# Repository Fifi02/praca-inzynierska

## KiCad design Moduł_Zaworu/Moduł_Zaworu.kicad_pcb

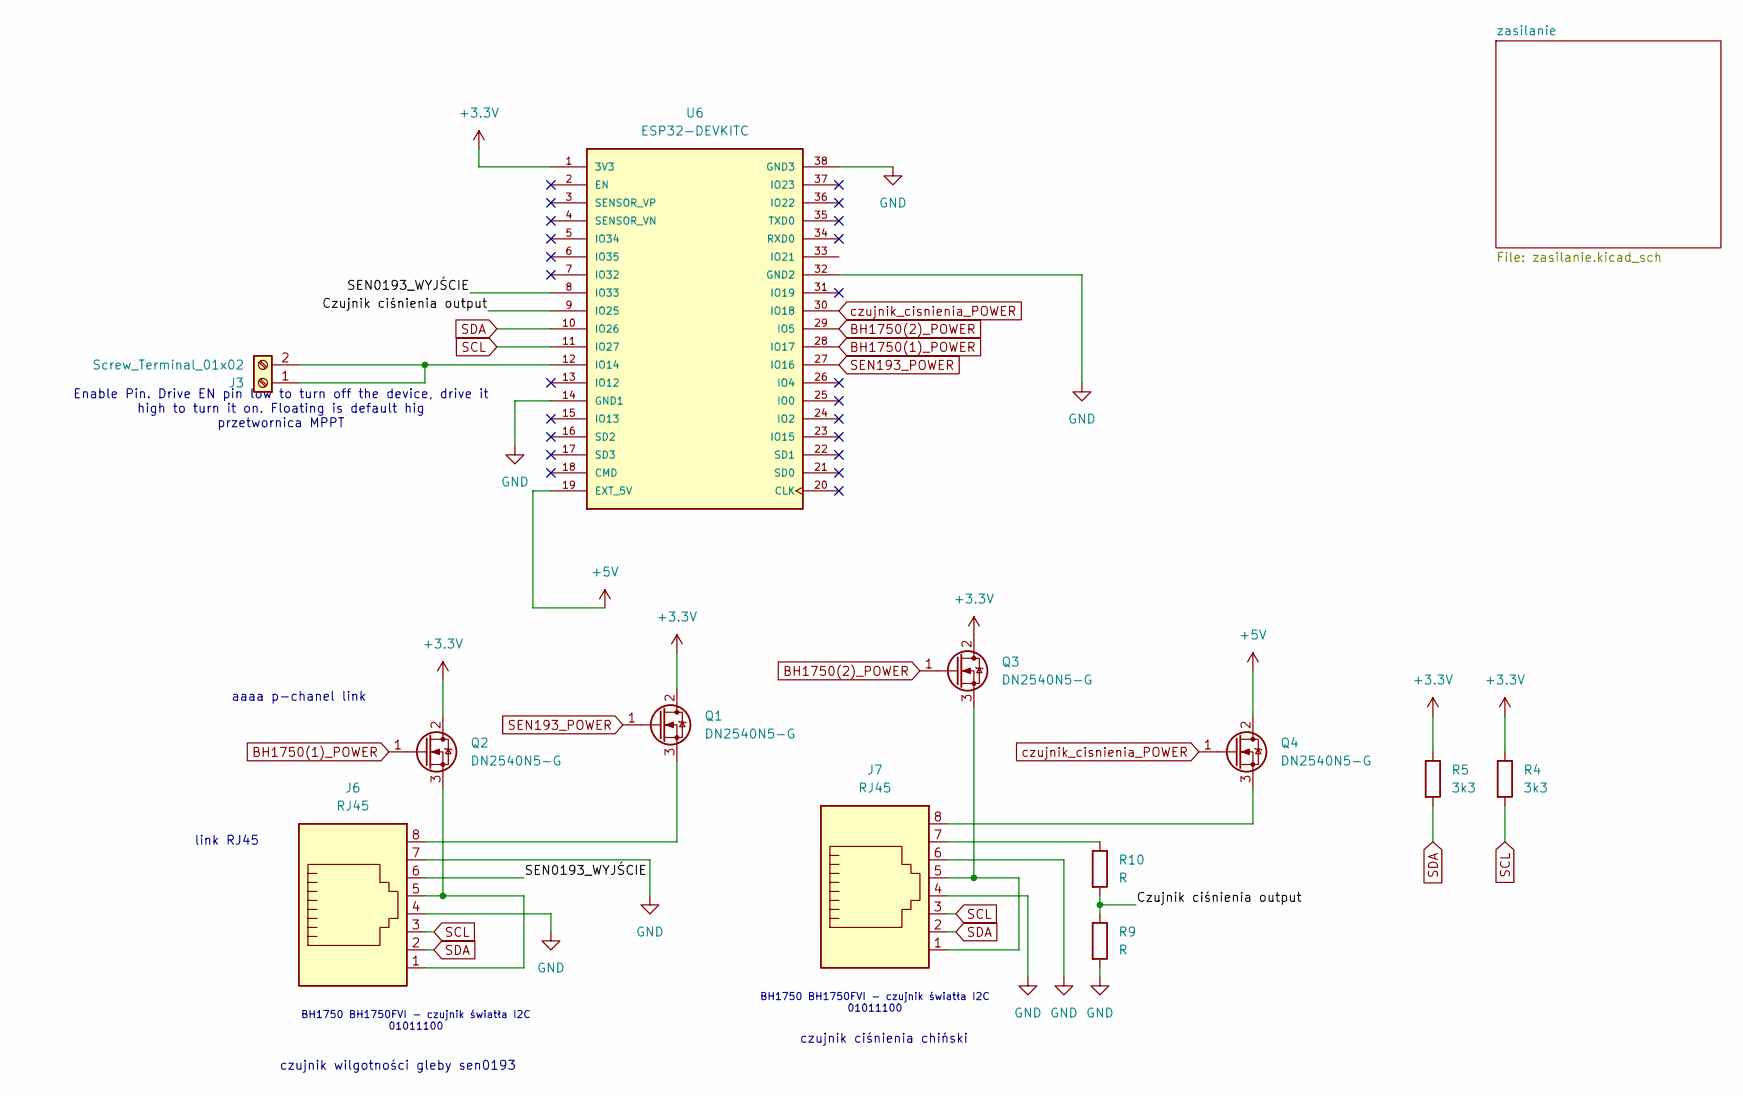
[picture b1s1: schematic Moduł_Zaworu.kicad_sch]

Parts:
J3: Screw_Terminal_01x02; TerminalBlock_Xinya_XY308-2.54-2P_1x02_P2.54mm_Horizontal
J6, J7: RJ45; RJ45_Amphenol_54602-x08_Horizontal
Q1, Q2, Q3, Q4: DN2540N5-G; SOT-23_Handsoldering
R4, R5: 3k3; R_1206_3216Metric
R9, R10: R; R_1206_3216Metric
U6: ESP32-DEVKITC; MODULE_ESP32-DEVKITC; PARTREV N/A

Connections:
+3.3V: Q1.2 (D), Q2.2 (D), Q3.2 (D), R4.1, R5.1, U6.1 (3V3); also elsewhere on the board
+5V: Q4.2 (D), U6.19 (EXT_5V); also elsewhere on the board
/Czujnik ciśnienia output: R9.1, R10.2, U6.9 (IO25)
/SEN0193_WYJŚCIE: J6.6, U6.8 (IO33)
BH1750(1)_POWER: Q2.1 (G), U6.28 (IO17)
BH1750(2)_POWER: Q3.1 (G), U6.29 (IO5)
GND: J6.4, J6.7, J7.4, J7.6, R9.2, U6.14 (GND1), U6.32 (GND2), U6.38 (GND3); also elsewhere on the board
unnamed: J3.1, J3.2, U6.12 (IO14)
unnamed: J7.7, R10.1
unnamed: J6.8, Q1.3 (S)
unnamed: J6.1, J6.5, Q2.3 (S)
unnamed: J7.1, J7.5, Q3.3 (S)
unnamed: J7.8, Q4.3 (S)
SCL: J6.3, J7.3, R4.2, U6.11 (IO27); also elsewhere on the board
SDA: J6.2, J7.2, R5.2, U6.10 (IO26); also elsewhere on the board
SEN193_POWER: Q1.1 (G), U6.27 (IO16)
czujnik_cisnienia_POWER: Q4.1 (G), U6.30 (IO18)

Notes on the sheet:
BH1750 BH1750FVI - czujnik światła I2C 01011100
Enable Pin. Drive EN pin low to turn off the device, drive it high to turn it on. Floating is default hig przetwornica MPPT
link RJ45
aaaa p-chanel link
czujnik wilgotności gleby sen0193
czujnik ciśnienia chiński

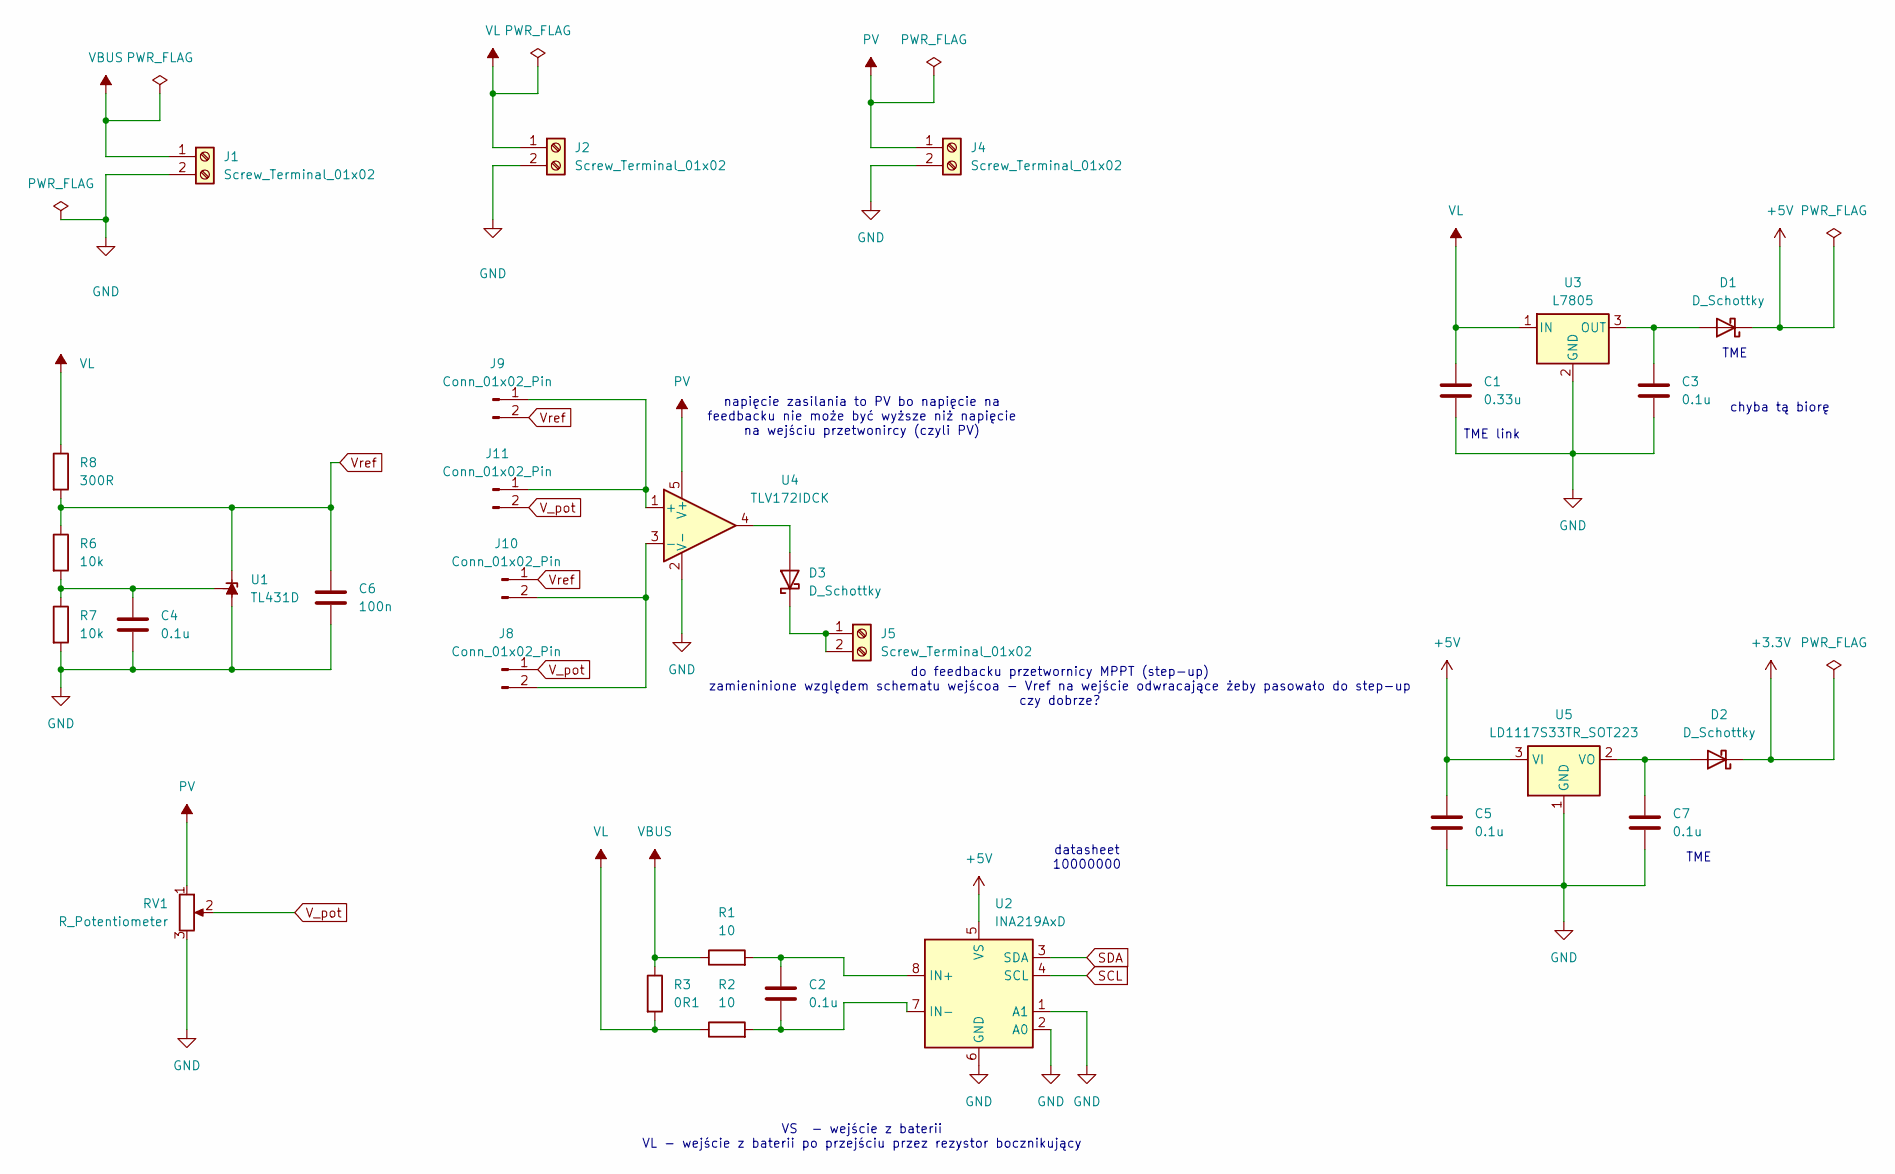
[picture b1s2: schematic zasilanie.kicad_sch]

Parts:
C1: 0.33u; CP_Elec_4x5.4
C2, C3, C4, C5, C7: 0.1u; C_Disc_D3.0mm_W1.6mm_P2.50mm
C6: 100n; C_Disc_D3.0mm_W1.6mm_P2.50mm
D1, D2, D3: D_Schottky; D_1206_3216Metric
J1, J2, J4: Screw_Terminal_01x02; TerminalBlock_MaiXu_MX126-5.0-02P_1x02_P5.00mm
J5: Screw_Terminal_01x02; TerminalBlock_Xinya_XY308-2.54-2P_1x02_P2.54mm_Horizontal
J8, J9, J10, J11: Conn_01x02_Pin; PinHeader_1x02_P2.54mm_Vertical
R1, R2: 10; R_1206_3216Metric
R3: 0R1; R_1206_3216Metric
R6, R7: 10k; R_1206_3216Metric
R8: 300R; R_1206_3216Metric
RV1: R_Potentiometer; Potentiometer_Bourns_3386W_Horizontal
U1: TL431D; SOIC-8_3.9x4.9mm_P1.27mm
U2: INA219AxD; SOIC-8_3.9x4.9mm_P1.27mm
U3: L7805; TO-220-3_Vertical
U4: TLV172IDCK; SOIC-8_5.3x5.3mm_P1.27mm
U5: LD1117S33TR_SOT223; SOT-223

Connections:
+3.3V: D2.1 (K); also elsewhere on the board
+5V: C5.1, D1.1 (K), U2.5 (VS), U5.3 (VI); also elsewhere on the board
GND: C1.2, C3.2, C4.2, C5.2, C6.2, C7.2, J1.2, J2.2, J4.2, R7.2, RV1.3, U1.2 (A), U1.3 (A), U1.6 (A), U1.7 (A), U2.1 (A1), U2.2 (A0), U2.6 (GND), U3.2 (GND), U4.2 (V-), U5.1 (GND); also elsewhere on the board
unnamed: C3.1, D1.2 (A), U3.3 (OUT)
unnamed: C7.1, D2.2 (A), U5.2 (VO)
unnamed: D3.2 (A), U4.4
unnamed: D3.1 (K), J5.1, J5.2
unnamed: J8.2, J10.2, U4.3 (-)
unnamed: J9.1, J11.1, U4.1 (+)
unnamed: C4.1, R6.2, R7.1, U1.8 (REF)
unnamed: C2.1, R1.2, U2.8 (IN+)
unnamed: C2.2, R2.2, U2.7 (IN-)
PV: J4.1, RV1.1, U4.5 (V+)
SCL: U2.4 (SCL); also elsewhere on the board
SDA: U2.3 (SDA); also elsewhere on the board
VBUS: J1.1, R1.1, R3.1
VL: C1.1, J2.1, R2.1, R3.2, R8.1, U3.1 (IN)
V_pot: J8.1, J11.2, RV1.2
Vref: C6.1, J9.2, J10.1, R6.1, R8.2, U1.1 (K)

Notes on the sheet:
do feedbacku przetwornicy MPPT (step-up) zamieninione względem schematu wejścoa - Vref na wejście odwracające żeby pasowało do step-up czy dobrze?
TME
TME link
datasheet 10000000
chyba tą biorę
napięcie zasilania to PV bo napięcie na feedbacku nie może być wyższe niż napięcie na wejściu przetwonircy (czyli PV)
VS - wejście z baterii VL - wejście z baterii po przejściu przez rezystor bocznikujący

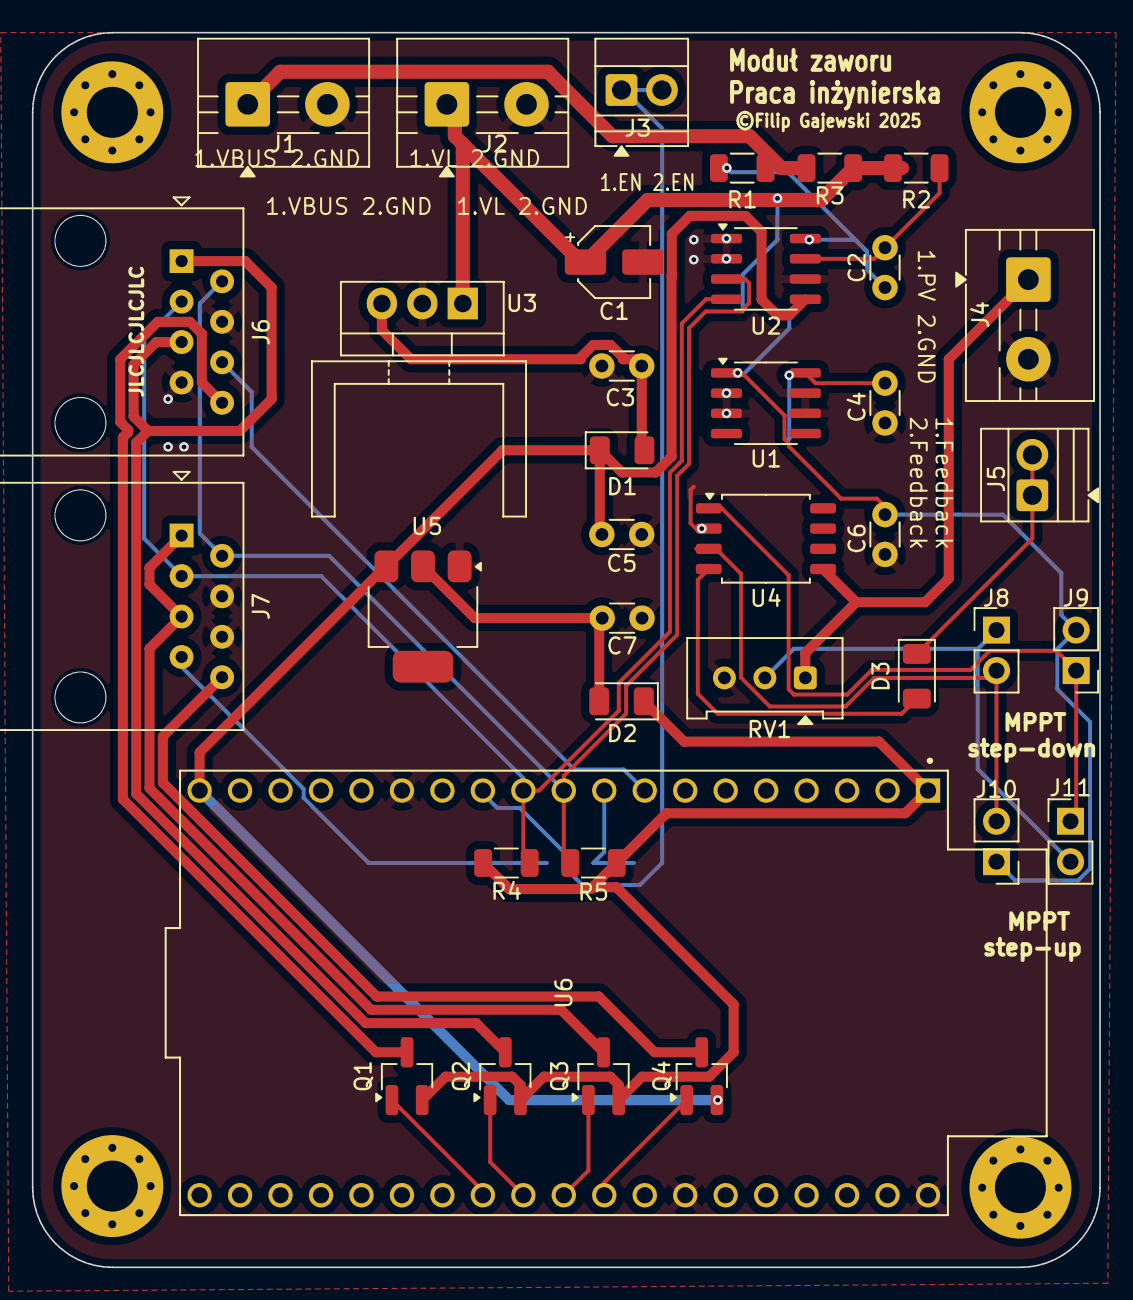
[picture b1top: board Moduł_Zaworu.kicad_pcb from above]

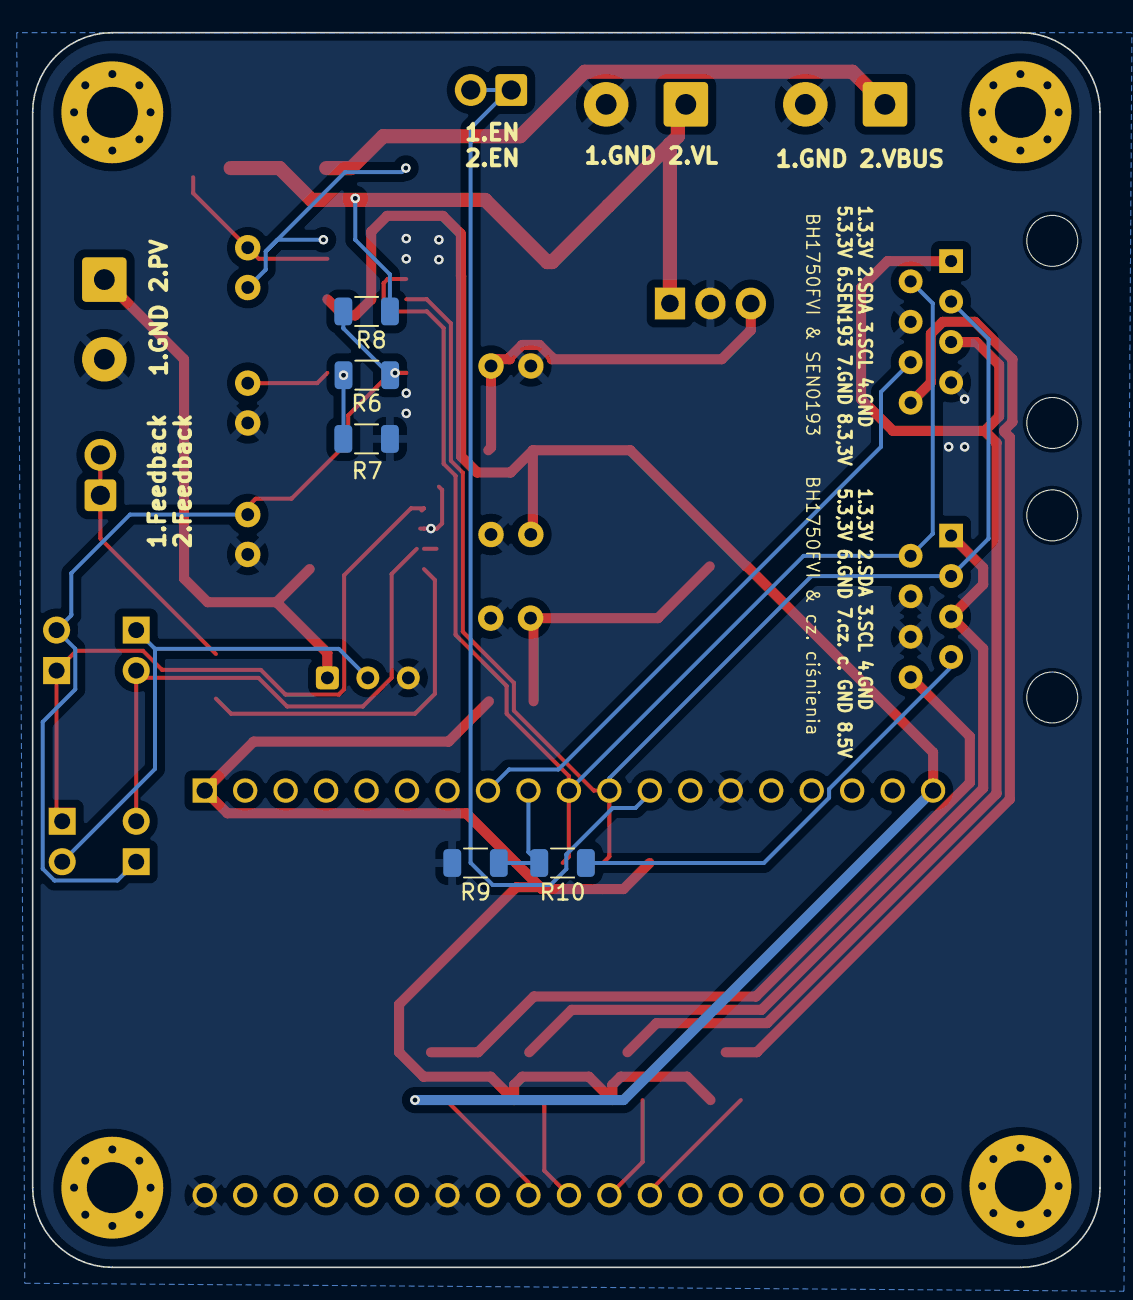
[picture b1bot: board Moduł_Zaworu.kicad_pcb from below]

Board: 2 copper layers, 67.0 x 77.5 mm, 42 parts (5 on the bottom side), 31 nets.

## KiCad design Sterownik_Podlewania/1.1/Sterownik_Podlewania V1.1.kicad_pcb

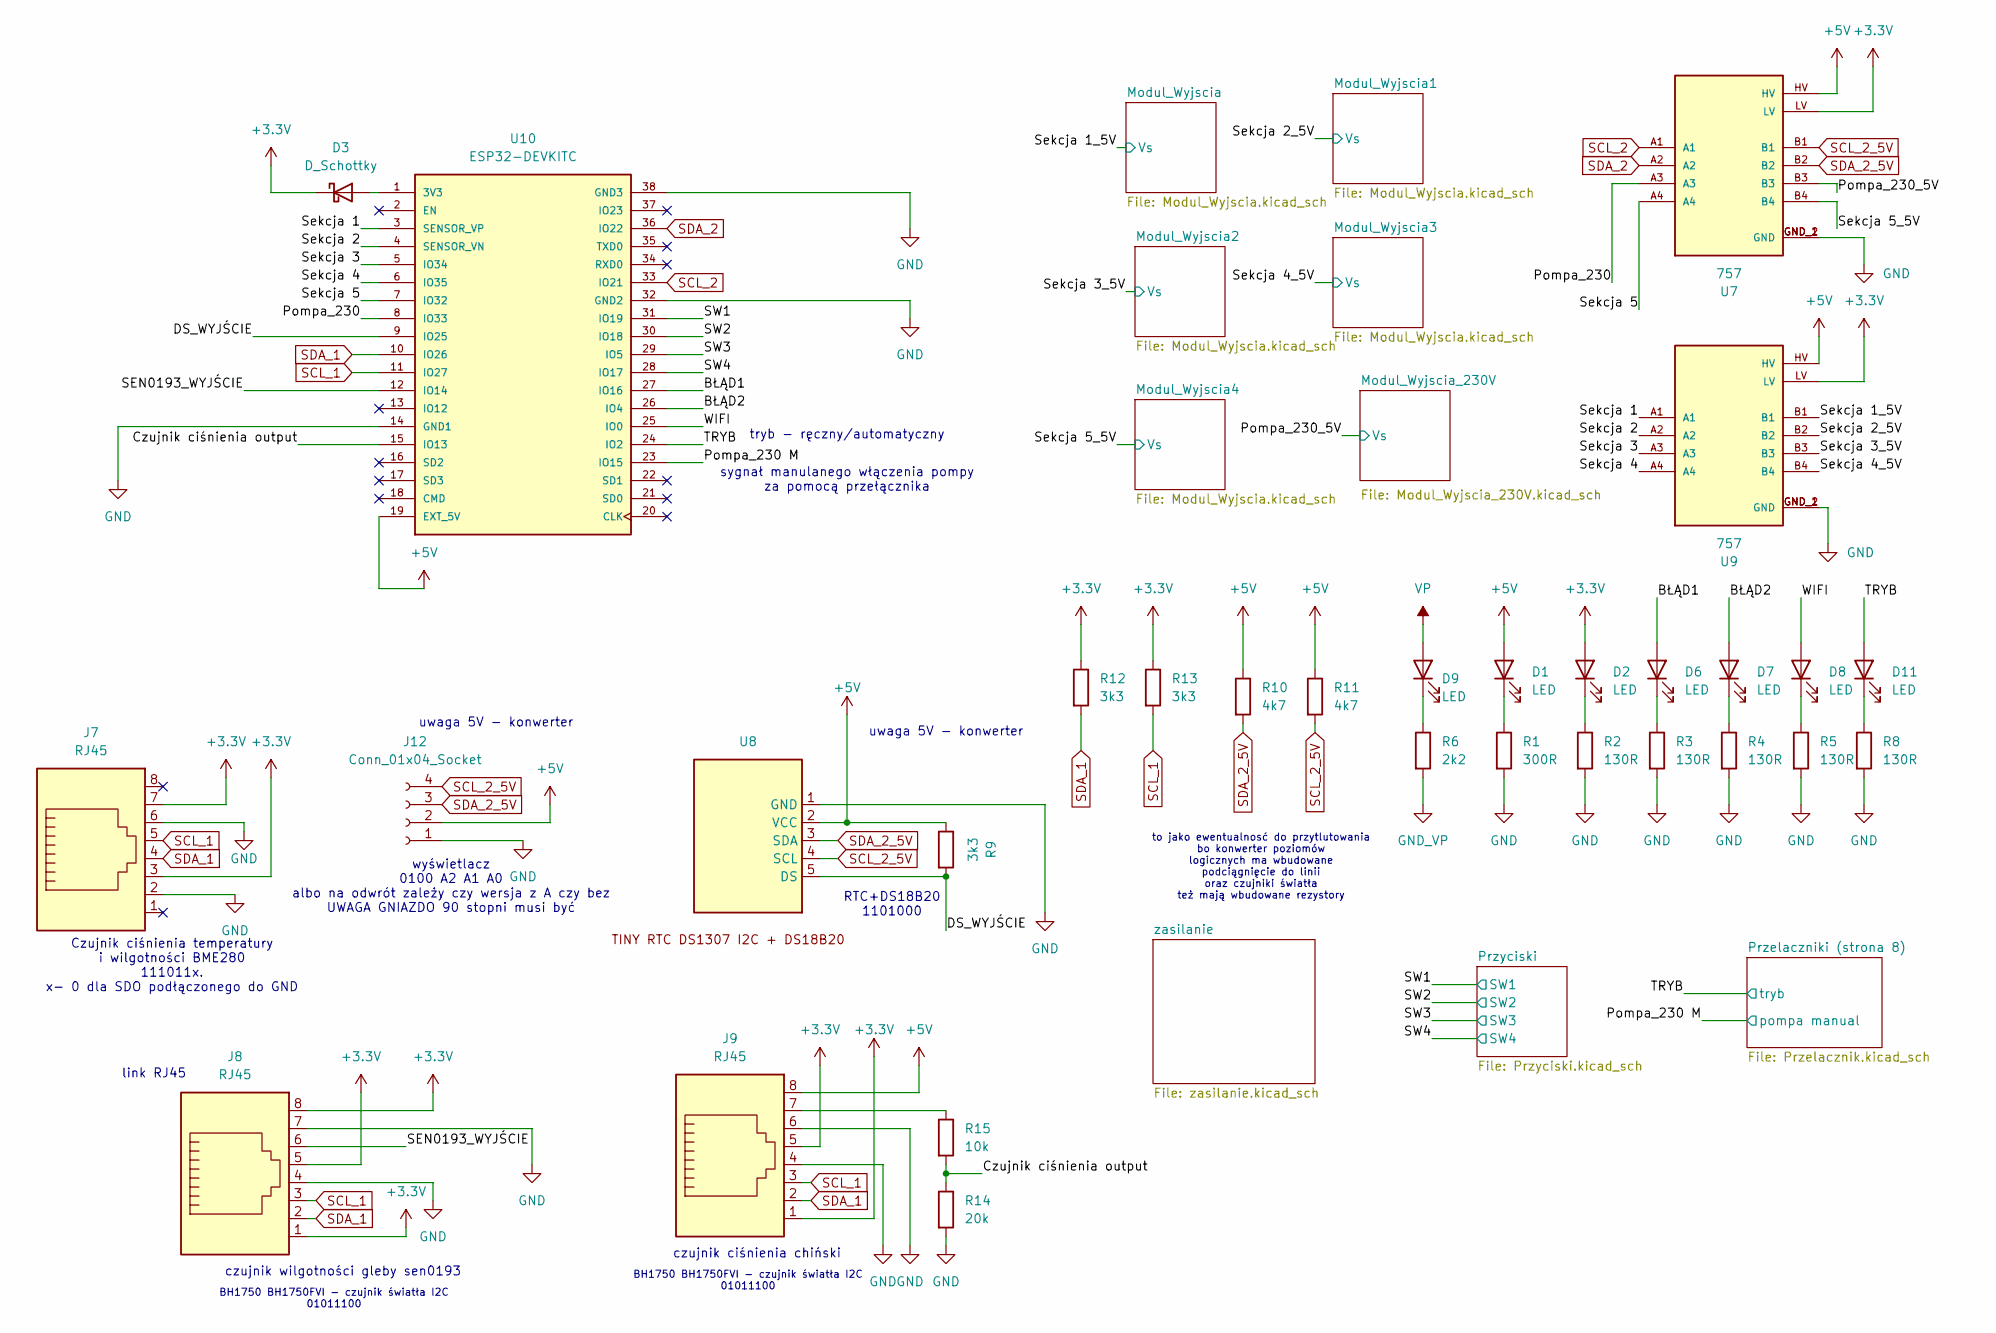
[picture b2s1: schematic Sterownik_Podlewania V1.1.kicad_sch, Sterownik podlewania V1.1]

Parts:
D1, D2, D6, D7, D8, D9, D11: LED; LED_1206_3216Metric
D3: D_Schottky; D_1206_3216Metric
J7, J8, J9: RJ45; RJ45_Amphenol_54602-x08_Horizontal
J12: Conn_01x04_Socket; PinHeader_1x04_P2.54mm_Vertical
R1: 300R; R_1206_3216Metric
R2, R3, R4, R5, R8: 130R; R_1206_3216Metric
R6: 2k2; R_1206_3216Metric
R9, R12, R13: 3k3; R_1206_3216Metric
R10, R11: 4k7; R_1206_3216Metric
R14: 20k; R_1206_3216Metric
R15: 10k; R_1206_3216Metric
U7, U9: 757; MODULE_757; PARTREV N/A
U8: RTC DS1307 + 32kb EEPROM 24C32 I2C
U10: ESP32-DEVKITC; MODULE_ESP32-DEVKITC; PARTREV N/A

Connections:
+3.3V: D2.2 (A), D3.1 (K), J7.3, J7.7, J8.1, J8.5, J8.8, J9.1, J9.5, R12.1, R13.1, U7.LV, U9.LV; also elsewhere on the board
+5V: D1.2 (A), J9.8, J12.2, R9.1, R10.1, R11.1, U7.HV, U8.2 (VCC), U9.HV, U10.19 (EXT_5V); also elsewhere on the board
/BŁĄD1: D6.2 (A), U10.27 (IO16)
/BŁĄD2: D7.2 (A), U10.26 (IO4)
/Czujnik ciśnienia output: R14.1, R15.2, U10.15 (IO13)
/DS_WYJŚCIE: R9.2, U8.5 (DS), U10.9 (IO25)
/Pompa_230: U7.A3, U10.8 (IO33)
/Pompa_230 M: U10.23 (IO15); also elsewhere on the board
/Pompa_230_5V: U7.B3; also elsewhere on the board
/SEN0193_WYJŚCIE: J8.6, U10.12 (IO14)
/SW1: U10.31 (IO19); also elsewhere on the board
/SW2: U10.30 (IO18); also elsewhere on the board
/SW3: U10.29 (IO5); also elsewhere on the board
/SW4: U10.28 (IO17); also elsewhere on the board
/Sekcja 1: U9.A1, U10.3 (SENSOR_VP)
/Sekcja 1_5V: U9.B1; also elsewhere on the board
/Sekcja 2: U9.A2, U10.4 (SENSOR_VN)
/Sekcja 2_5V: U9.B2; also elsewhere on the board
/Sekcja 3: U9.A3, U10.5 (IO34)
/Sekcja 3_5V: U9.B3; also elsewhere on the board
/Sekcja 4: U9.A4, U10.6 (IO35)
/Sekcja 4_5V: U9.B4; also elsewhere on the board
/Sekcja 5: U7.A4, U10.7 (IO32)
/Sekcja 5_5V: U7.B4; also elsewhere on the board
/TRYB: D11.2 (A), U10.24 (IO2); also elsewhere on the board
/WIFI: D8.2 (A), U10.25 (IO0)
GND: J7.2, J7.6, J8.4, J8.7, J9.4, J9.6, J12.1, R1.2, R2.2, R3.2, R4.2, R5.2, R8.2, R14.2, U7.GND_1 (GND), U7.GND_2 (GND), U8.1 (GND), U9.GND_1 (GND), U9.GND_2 (GND), U10.14 (GND1), U10.32 (GND2), U10.38 (GND3); also elsewhere on the board
GND_VP: R6.2; also elsewhere on the board
unnamed: D1.1 (K), R1.1
unnamed: D2.1 (K), R2.1
unnamed: D3.2 (A), U10.1 (3V3)
unnamed: D6.1 (K), R3.1
unnamed: D7.1 (K), R4.1
unnamed: D8.1 (K), R5.1
unnamed: D9.1 (K), R6.1
unnamed: D11.1 (K), R8.1
unnamed: J9.7, R15.1
SCL_1: J7.5, J8.3, J9.3, R13.2, U10.11 (IO27)
SCL_2: U7.A1, U10.33 (IO21)
SCL_2_5V: J12.4, R11.2, U7.B1, U8.4 (SCL)
SDA_1: J7.4, J8.2, J9.2, R12.2, U10.10 (IO26)
SDA_2: U7.A2, U10.36 (IO22)
SDA_2_5V: J12.3, R10.2, U7.B2, U8.3 (SDA)
VP: D9.2 (A); also elsewhere on the board

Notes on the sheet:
BH1750 BH1750FVI - czujnik światła I2C 01011100
uwaga 5V - konwerter
czujnik wilgotności gleby sen0193
sygnał manulanego włączenia pompy za pomocą przełącznika
tryb - ręczny/automatyczny
to jako ewentualnosć do przytlutowania bo konwerter poziomów logicznych ma wbudowane podciągnięcie do linii oraz czujniki światła też mają wbudowane rezystory
link RJ45
wyświetlacz 0100 A2 A1 A0 albo na odwrót zależy czy wersja z A czy bez UWAGA GNIAZDO 90 stopni musi być
Czujnik ciśnienia temperatury i wilgotności BME280 111011x. x- 0 dla SDO podłączonego do GND
czujnik ciśnienia chiński
RTC+DS18B20 1101000

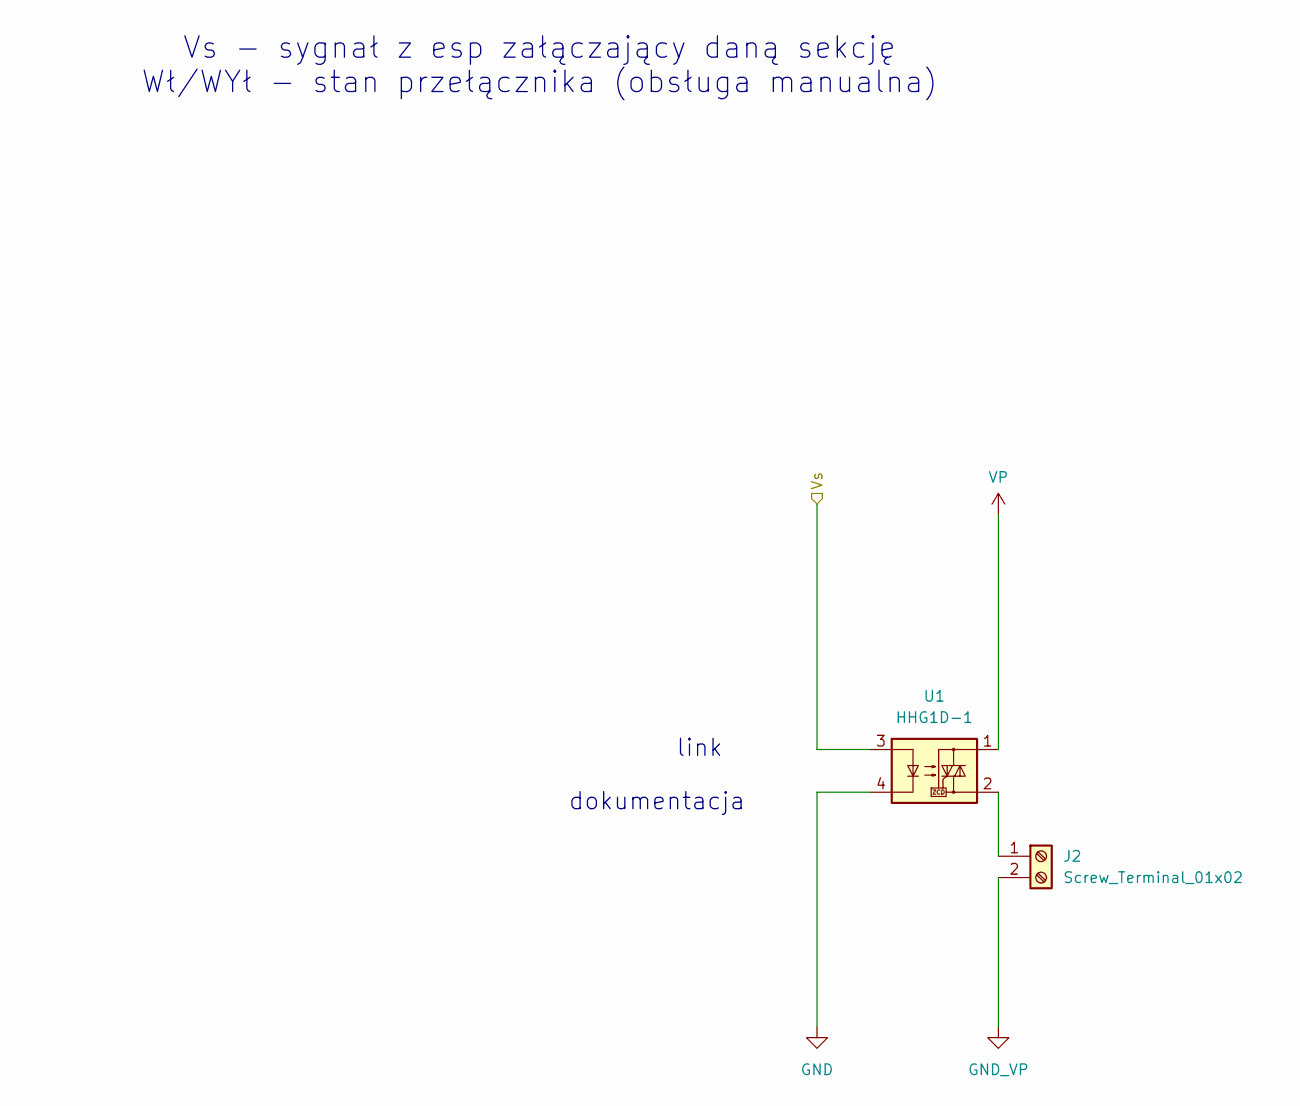
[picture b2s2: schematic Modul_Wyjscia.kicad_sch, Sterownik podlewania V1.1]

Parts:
J2: Screw_Terminal_01x02; TerminalBlock_MaiXu_MX126-5.0-02P_1x02_P5.00mm
U1: HHG1D-1; RELAY_G3MB-202P

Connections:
/Sekcja 1_5V: U1.3; also elsewhere on the board
GND: U1.4; also elsewhere on the board
GND_VP: J2.2; also elsewhere on the board
unnamed: J2.1, U1.2
VP: U1.1; also elsewhere on the board

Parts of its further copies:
J3, J4, J5, J6: Screw_Terminal_01x02; TerminalBlock_MaiXu_MX126-5.0-02P_1x02_P5.00mm
U2, U3, U4, U5: HHG1D-1; RELAY_G3MB-202P

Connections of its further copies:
/Sekcja 2_5V: U2.3; also elsewhere on the board
/Sekcja 3_5V: U3.3; also elsewhere on the board
/Sekcja 4_5V: U4.3; also elsewhere on the board
/Sekcja 5_5V: U5.3; also elsewhere on the board
GND: U2.4, U3.4, U4.4, U5.4; also elsewhere on the board
GND_VP: J3.2, J4.2, J5.2, J6.2; also elsewhere on the board
unnamed: J3.1, U2.2
unnamed: J4.1, U3.2
unnamed: J5.1, U4.2
unnamed: J6.1, U5.2
VP: U2.1, U3.1, U4.1, U5.1; also elsewhere on the board

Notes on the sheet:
Vs - sygnał z esp załączający daną sekcję Wł/WYł - stan przełącznika (obsługa manualna)
dokumentacja
link

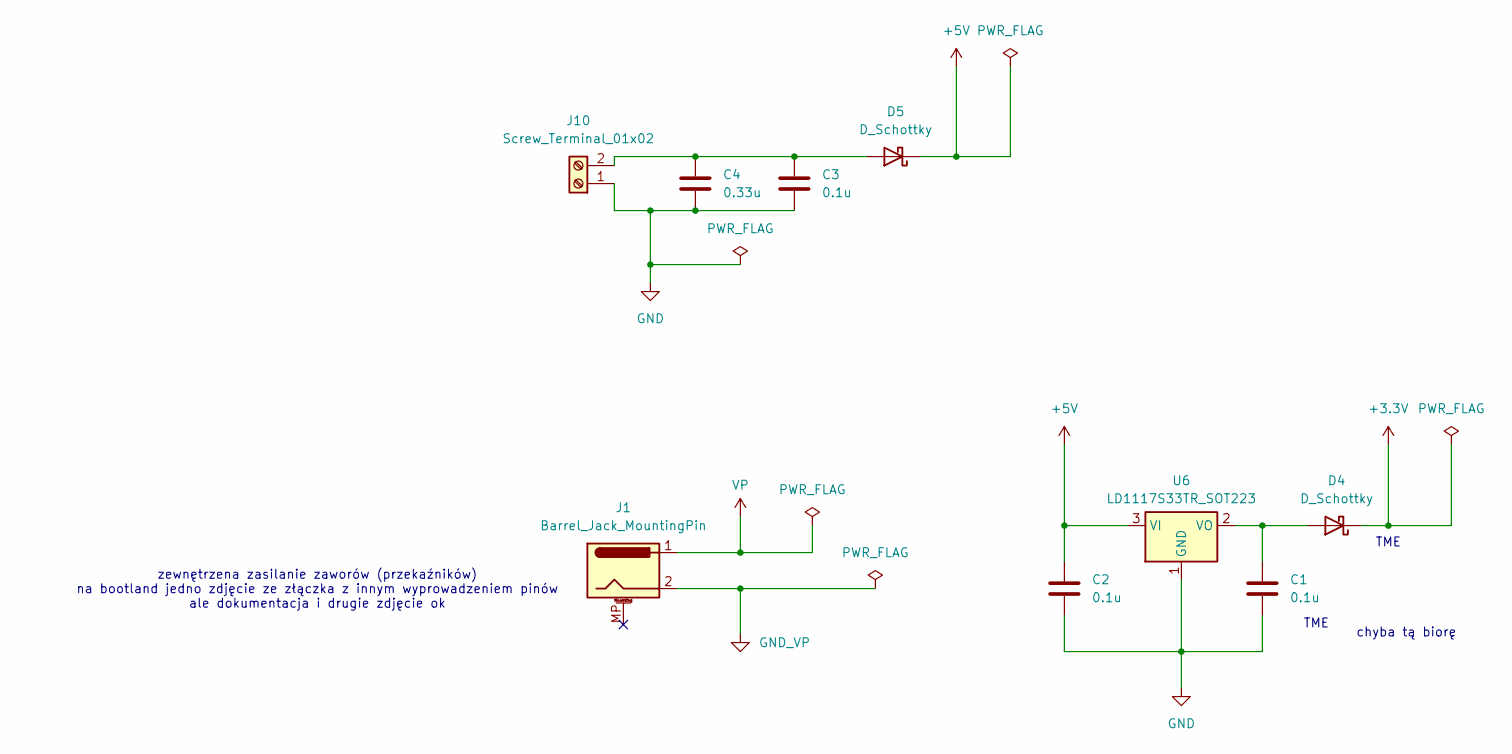
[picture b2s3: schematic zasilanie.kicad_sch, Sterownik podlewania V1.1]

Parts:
C1, C2, C3: 0.1u; C_Disc_D3.0mm_W1.6mm_P2.50mm
C4: 0.33u; CP_Elec_4x5.4
D4, D5: D_Schottky; D_1206_3216Metric
J1: Barrel_Jack_MountingPin; BarrelJack_GCT_DCJ200-10-A_Horizontal
J10: Screw_Terminal_01x02; TerminalBlock_MaiXu_MX126-5.0-02P_1x02_P5.00mm
U6: LD1117S33TR_SOT223; SOT-223

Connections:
+3.3V: D4.1 (K); also elsewhere on the board
+5V: C2.1, D5.1 (K), U6.3 (VI); also elsewhere on the board
GND: C1.2, C2.2, C3.2, C4.2, J10.1, U6.1 (GND); also elsewhere on the board
GND_VP: J1.2; also elsewhere on the board
unnamed: C1.1, D4.2 (A), U6.2 (VO)
unnamed: C3.1, C4.1, D5.2 (A), J10.2
VP: J1.1; also elsewhere on the board

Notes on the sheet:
TME
chyba tą biorę
zewnętrzena zasilanie zaworów (przekaźników) na bootland jedno zdjęcie ze złączka z innym wyprowadzeniem pinów ale dokumentacja i drugie zdjęcie ok

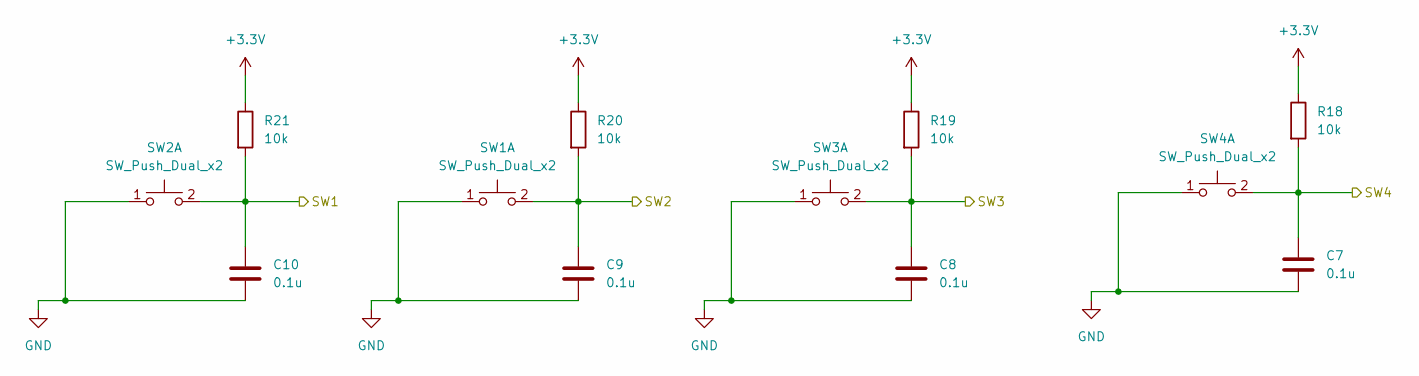
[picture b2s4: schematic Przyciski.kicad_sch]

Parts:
C7, C8, C9, C10: 0.1u; C_1206_3216Metric
R18, R19, R20, R21: 10k; R_1206_3216Metric
SW1, SW2, SW3, SW4: SW_Push_Dual_x2; SW_PUSH_6mm

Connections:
+3.3V: R18.1, R19.1, R20.1, R21.1; also elsewhere on the board
/SW1: C10.1, R21.2, SW2.2 (D); also elsewhere on the board
/SW2: C9.1, R20.2, SW1.2 (D); also elsewhere on the board
/SW3: C8.1, R19.2, SW3.2 (D); also elsewhere on the board
/SW4: C7.1, R18.2, SW4.2 (D); also elsewhere on the board
GND: C7.2, C8.2, C9.2, C10.2, SW1.1 (C), SW2.1 (C), SW3.1 (C), SW4.1 (C); also elsewhere on the board

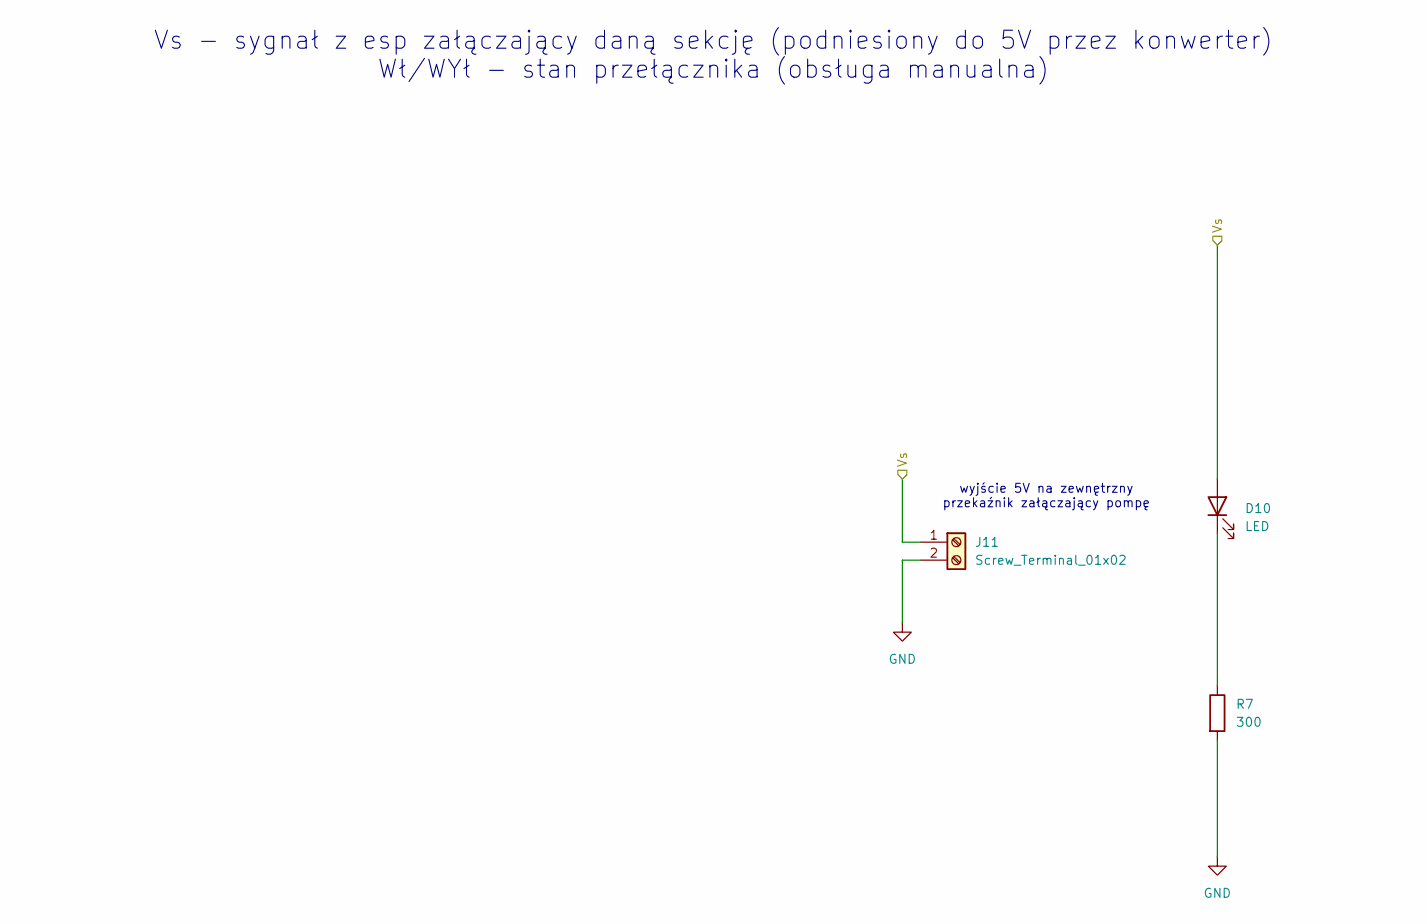
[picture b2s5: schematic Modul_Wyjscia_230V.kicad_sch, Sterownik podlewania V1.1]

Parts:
D10: LED; LED_1206_3216Metric
J11: Screw_Terminal_01x02; TerminalBlock_MaiXu_MX126-5.0-02P_1x02_P5.00mm
R7: 300; R_1206_3216Metric

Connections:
/Pompa_230_5V: D10.2 (A), J11.1; also elsewhere on the board
GND: J11.2, R7.2; also elsewhere on the board
unnamed: D10.1 (K), R7.1

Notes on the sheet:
wyjście 5V na zewnętrzny przekaźnik załączający pompę
Vs - sygnał z esp załączający daną sekcję (podniesiony do 5V przez konwerter) Wł/WYł - stan przełącznika (obsługa manualna)

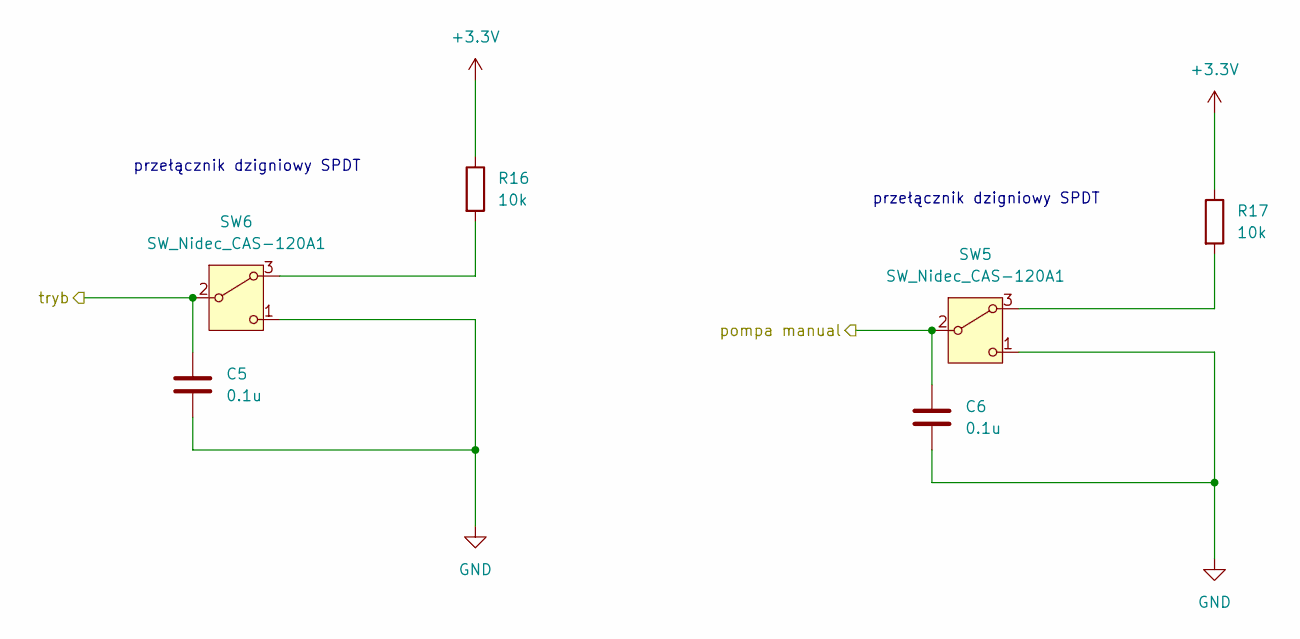
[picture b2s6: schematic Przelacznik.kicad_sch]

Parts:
C5, C6: 0.1u; C_1206_3216Metric
R16, R17: 10k; R_1206_3216Metric
SW5, SW6: SW_Nidec_CAS-120A1; Toggle Switch Bootland 4.7mm

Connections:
+3.3V: R16.1, R17.1; also elsewhere on the board
/Pompa_230 M: C6.1, SW5.2 (B); also elsewhere on the board
/TRYB: C5.1, SW6.2 (B); also elsewhere on the board
GND: C5.2, C6.2, SW5.1 (C), SW6.1 (C); also elsewhere on the board
unnamed: R17.2, SW5.3 (A)
unnamed: R16.2, SW6.3 (A)

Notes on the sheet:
przełącznik dzigniowy SPDT

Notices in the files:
Moduł_Zaworu/Moduł_Zaworu.kicad_pcb:
©Filip Gajewski 2025
